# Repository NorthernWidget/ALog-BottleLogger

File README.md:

ALog-BottleLogger
=================

## Deprecation / update notice

The lovely ALog has a dear place in our hearts, but time flows by.

For our modern supported data loggers, see:
* [Project Margay](https://github.com/NorthernWidget-Skunkworks/Project-Margay): Small form factor ALog-like data logger, optimized for digital communications
* [Project Resnik](https://github.com/NorthernWidget-Skunkworks/Project-Resnik): Data logger for large installations, solar power, and telemetry

## ALog BottleLogger Basic Information

The ALog BottleLogger is an Arduino-based low-power field environmental data logging platform.

This repository contains hardware design files, centered around:
* Electronic schematics
* Circuit board layouts

In addition, the following are supplied, but are not always kept up-to-date in the main branch:
* Bill of materials (electronic components)
* Gerber files for circuit board production
* Pick-and-place files

## Layout Overview for End-Users

<!--

## Significant components

-->

## Citation

If you use this data logger in a publication, please cite:

**Wickert, A. D. (2014), [The ALog: Inexpensive, Open-Source, Automated Data Collection in the Field](https://doi.org/10.1890/0012-9623-95.2.68), *Bull. Ecol. Soc. Am.*, *95*(2), 68–78, doi:10.1890/0012-9623-95.2.68.**

**Wickert, A. D., C. T. Sandell, B. Schulz, and G.-H. C. Ng (2019), [Open-source Arduino-compatible data loggers designed for field research](https://doi.org/10.5194/hess-23-2065-2019), *Hydrol. Earth Syst. Sci.*, *23*, 2065–2076, doi:10.5194/hess-23-2065-2019.**

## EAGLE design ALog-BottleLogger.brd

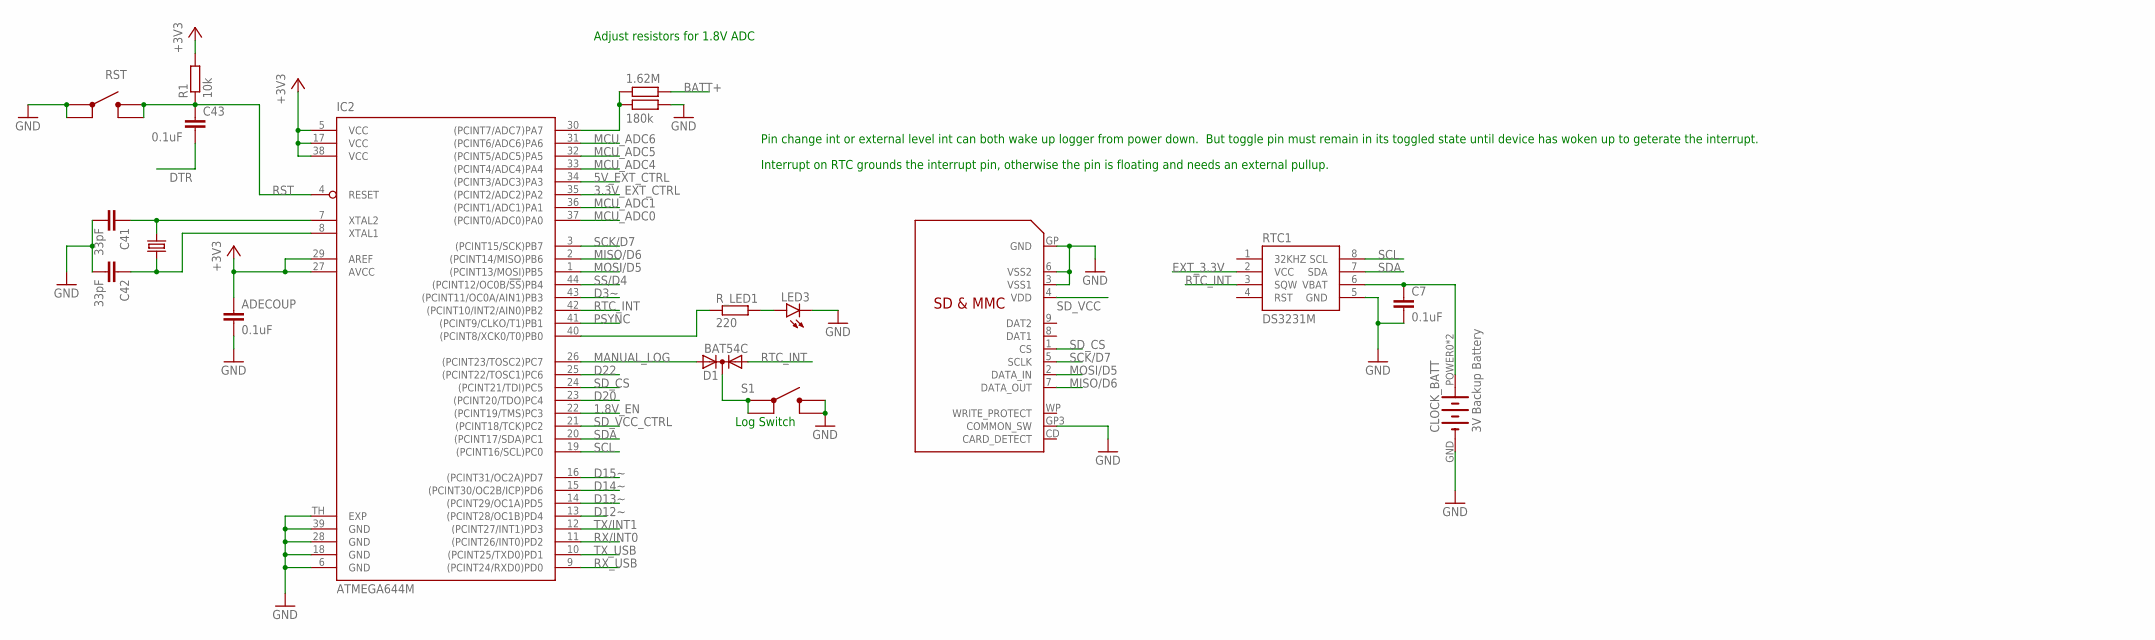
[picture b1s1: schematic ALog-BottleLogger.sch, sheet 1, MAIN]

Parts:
ADECOUP: 0.1uF; C0603
C7, C43: 0.1uF; C0603
C41, C42: 33pF; C0603
CLOCK_BATT: 3V Backup Battery; LINX_BAT-HLD-012-SMT
D1: BAT54C; SOT23C
IC2: ATMEGA644M; MLF44-TH
LED3: LED1206; LED-1206
Q3: CRYSTALHC49UP; HC49UP
R1: 10k; R0603
R18: 1.62M; R0603
R19: 180k; R0603
RTC1: DS3231M; SO08
R_LED1: 220; R0603
S1: SWITCHC&K_400GF; SWITCH_4.2X3.2
SD: SDMMC06132; 06132
U$4: SWITCHC&K_400GF; SWITCH_4.2X3.2

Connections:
1.8V_EN: IC2.22 ((PCINT19/TMS)PC3); also elsewhere on the board
3.3V_EXT_CTRL: IC2.35 ((PCINT2/ADC2)PA2); also elsewhere on the board
5V_EXT_CTRL: IC2.34 ((PCINT3/ADC3)PA3); also elsewhere on the board
+3V3: ADECOUP.1, IC2.5 (VCC), IC2.17 (VCC), IC2.27 (AVCC), IC2.29 (AREF), IC2.38 (VCC), R1.2; also elsewhere on the board
ADC16: IC2.30 ((PCINT7/ADC7)PA7), R18.1, R19.1
BATT+: R18.2; also elsewhere on the board
D3~: IC2.43 ((PCINT11/OC0A/AIN1)PB3); also elsewhere on the board
D12~: IC2.13 ((PCINT28/OC1B)PD4); also elsewhere on the board
D13~: IC2.14 ((PCINT29/OC1A)PD5); also elsewhere on the board
D14~: IC2.15 ((PCINT30/OC2B/ICP)PD6); also elsewhere on the board
D15~: IC2.16 ((PCINT31/OC2A)PD7); also elsewhere on the board
D20: IC2.23 ((PCINT20/TDO)PC4)
D22: IC2.25 ((PCINT22/TOSC1)PC6)
DTR: C43.2; also elsewhere on the board
EXT_3.3V: RTC1.2 (VCC); also elsewhere on the board
GND: ADECOUP.2, C7.2, C41.2, C42.2, CLOCK_BATT.GND (-), IC2.6 (GND), IC2.18 (GND), IC2.28 (GND), IC2.39 (GND), IC2.TH (EXP), LED3.C, R19.2, RTC1.5 (GND), S1.P$3 (3), S1.P$4 (4), SD.3 (VSS1), SD.6 (VSS2), SD.GP (GND), SD.GP3 (COMMON_SW), U$4.P$1 (1), U$4.P$2 (2); also elsewhere on the board
LED+1: LED3.A, R_LED1.2
MANUAL_LOG: D1.2 (A2), IC2.26 ((PCINT23/TOSC2)PC7)
MCU_ADC0: IC2.37 ((PCINT0/ADC0)PA0); also elsewhere on the board
MCU_ADC1: IC2.36 ((PCINT1/ADC1)PA1)
MCU_ADC4: IC2.33 ((PCINT4/ADC4)PA4)
MCU_ADC5: IC2.32 ((PCINT5/ADC5)PA5)
MCU_ADC6: IC2.31 ((PCINT6/ADC6)PA6)
MISO/D6: IC2.2 ((PCINT14/MISO)PB6), SD.7 (DATA_OUT); also elsewhere on the board
MOSI/D5: IC2.1 ((PCINT13/MOSI)PB5), SD.2 (DATA_IN); also elsewhere on the board
unnamed: IC2.40 ((PCINT8/XCK0/T0)PB0), R_LED1.1
unnamed: C7.1, CLOCK_BATT.POWER0 (+), CLOCK_BATT.POWER1 (+), RTC1.6 (VBAT)
unnamed: D1.3 (K), S1.P$1 (1), S1.P$2 (2)
PSYNC: IC2.41 ((PCINT9/CLKO/T1)PB1); also elsewhere on the board
RST: C43.1, IC2.4 (RESET), R1.1, U$4.P$3 (3), U$4.P$4 (4); also elsewhere on the board
RTC_INT: D1.1 (A1), IC2.42 ((PCINT10/INT2/AIN0)PB2), RTC1.3 (SQW)
RX/INT0: IC2.11 ((PCINT26/INT0)PD2); also elsewhere on the board
RX_USB: IC2.9 ((PCINT24/RXD0)PD0); also elsewhere on the board
SCK/D7: IC2.3 ((PCINT15/SCK)PB7), SD.5 (SCLK); also elsewhere on the board
SCL: IC2.19 ((PCINT16/SCL)PC0), RTC1.8 (SCL); also elsewhere on the board
SDA: IC2.20 ((PCINT17/SDA)PC1), RTC1.7 (SDA); also elsewhere on the board
SD_CS: IC2.24 ((PCINT21/TDI)PC5), SD.1 (CS)
SD_VCC: SD.4 (VDD); also elsewhere on the board
SD_VCC_CTRL: IC2.21 ((PCINT18/TCK)PC2); also elsewhere on the board
SS/D4: IC2.44 ((PCINT12/OC0B/!SS!)PB4); also elsewhere on the board
TX/INT1: IC2.12 ((PCINT27/INT1)PD3); also elsewhere on the board
TX_USB: IC2.10 ((PCINT25/TXD0)PD1); also elsewhere on the board
XTAL1: C42.1, IC2.8 (XTAL1), Q3.1
XTAL2: C41.1, IC2.7 (XTAL2), Q3.2

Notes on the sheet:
Log Switch
Adjust resistors for 1.8V ADC
Pin change int or external level int can both wake up logger from power down. But toggle pin must remain in its toggled state until device has woken up to geterate the interrupt.
Interrupt on RTC grounds the interrupt pin, otherwise the pin is floating and needs an external pullup.

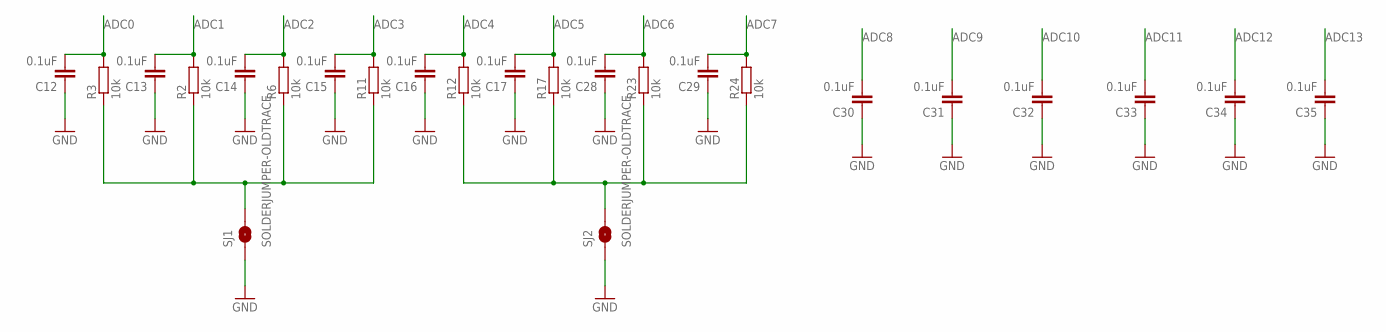
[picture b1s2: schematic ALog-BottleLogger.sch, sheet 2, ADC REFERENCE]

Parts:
C12, C13, C14, C15, C16, C17, C28, C29, C30, C31, C32, C33, C34, C35: 0.1uF; C0603
R2, R3, R6, R11, R12, R17, R23, R24: 10k; R0603
SJ1, SJ2: SOLDERJUMPER-OLDTRACE; SJ_2S-TRACE

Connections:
ADC0: C12.2, R3.2; also elsewhere on the board
ADC1: C13.2, R2.2; also elsewhere on the board
ADC2: C14.2, R6.2; also elsewhere on the board
ADC3: C15.2, R11.2; also elsewhere on the board
ADC4: C16.2, R12.2; also elsewhere on the board
ADC5: C17.2, R17.2; also elsewhere on the board
ADC6: C28.2, R23.2; also elsewhere on the board
ADC7: C29.2, R24.2; also elsewhere on the board
ADC8: C30.2; also elsewhere on the board
ADC9: C31.2; also elsewhere on the board
ADC10: C32.2; also elsewhere on the board
ADC11: C33.2; also elsewhere on the board
ADC12: C34.2; also elsewhere on the board
ADC13: C35.2; also elsewhere on the board
GND: C12.1, C13.1, C14.1, C15.1, C16.1, C17.1, C28.1, C29.1, C30.1, C31.1, C32.1, C33.1, C34.1, C35.1, SJ1.1, SJ2.1; also elsewhere on the board
unnamed: R12.1, R17.1, R23.1, R24.1, SJ2.2
unnamed: R2.1, R3.1, R6.1, R11.1, SJ1.2

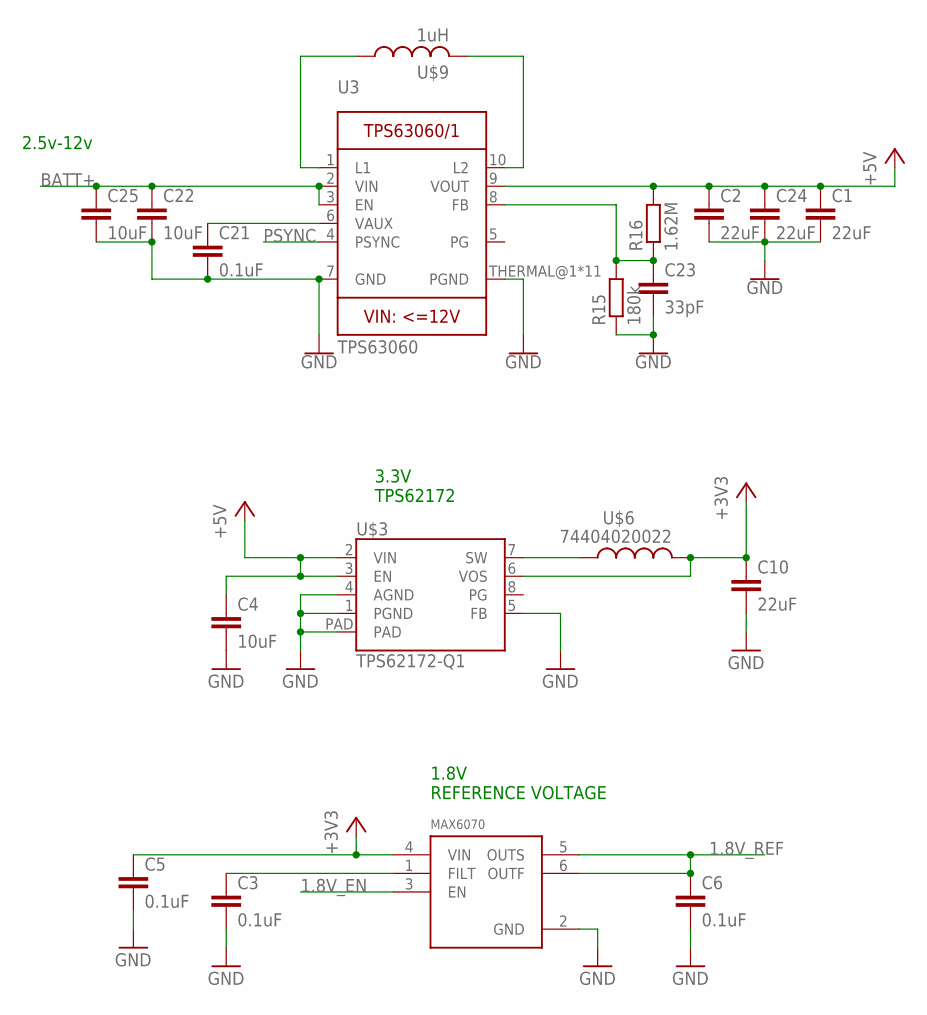
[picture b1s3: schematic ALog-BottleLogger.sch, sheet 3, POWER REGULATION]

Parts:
C1, C2, C10, C24: 22uF; C0805
C3, C5, C6, C21: 0.1uF; C0603
C4, C22, C25: 10uF; C0805
C23: 33pF; C0603
R15: 180k; R0603
R16: 1.62M; R0603
U3: TPS63060; PWSON-N10
U$2: MAX6070AAUT18; SOT23-6L
U$3: TPS62172-Q1; WSON-8-PAD
U$6: 74404020022; WURTH2.2UF
U$9: 1uH; WE-MAIA(4.1X4.1)

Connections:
1.8V_EN: U$2.3 (EN); also elsewhere on the board
1.8V_REF: C6.1, U$2.5 (OUTS), U$2.6 (OUTF); also elsewhere on the board
+3V3: C5.1, C10.1, U$2.4 (VIN), U$3.6 (VOS), U$6.2; also elsewhere on the board
+5V: C1.1, C2.1, C4.1, C24.1, R16.2, U3.9 (VOUT), U$3.2 (VIN), U$3.3 (EN); also elsewhere on the board
BATT+: C22.1, C25.1, U3.2 (VIN), U3.3 (EN); also elsewhere on the board
GND: C1.2, C2.2, C3.2, C4.2, C5.2, C6.2, C10.2, C21.2, C22.2, C23.2, C24.2, C25.2, R15.1, U3.7 (GND), U3.THERMAL@1 (PGND), U3.THERMAL@5 (PGND), U3.THERMAL@6 (PGND), U3.THERMAL@7 (PGND), U3.THERMAL@8 (PGND), U3.THERMAL@9 (PGND), U3.THERMAL@10 (PGND), U3.THERMAL@11 (PGND), U3.THERMAL@12 (PGND), U3.THERMAL@13 (PGND), U3.THERMAL@14 (PGND), U$2.2 (GND), U$3.1 (PGND), U$3.4 (AGND), U$3.5 (FB), U$3.PAD; also elsewhere on the board
unnamed 42: U$3.7 (SW), U$6.1; also elsewhere on the board
unnamed: C21.1, U3.6 (VAUX)
unnamed: C23.1, R15.2, R16.1, U3.8 (FB)
unnamed 67: U3.1 (L1), U$9.P$1 (1); also elsewhere on the board
unnamed 71: U3.10 (L2), U$9.P$2 (2); also elsewhere on the board
unnamed: C3.1, U$2.1 (FILT)
PSYNC: U3.4 (PSYNC); also elsewhere on the board

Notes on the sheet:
2.5v-12v
3.3V TPS62172
1.8V REFERENCE VOLTAGE

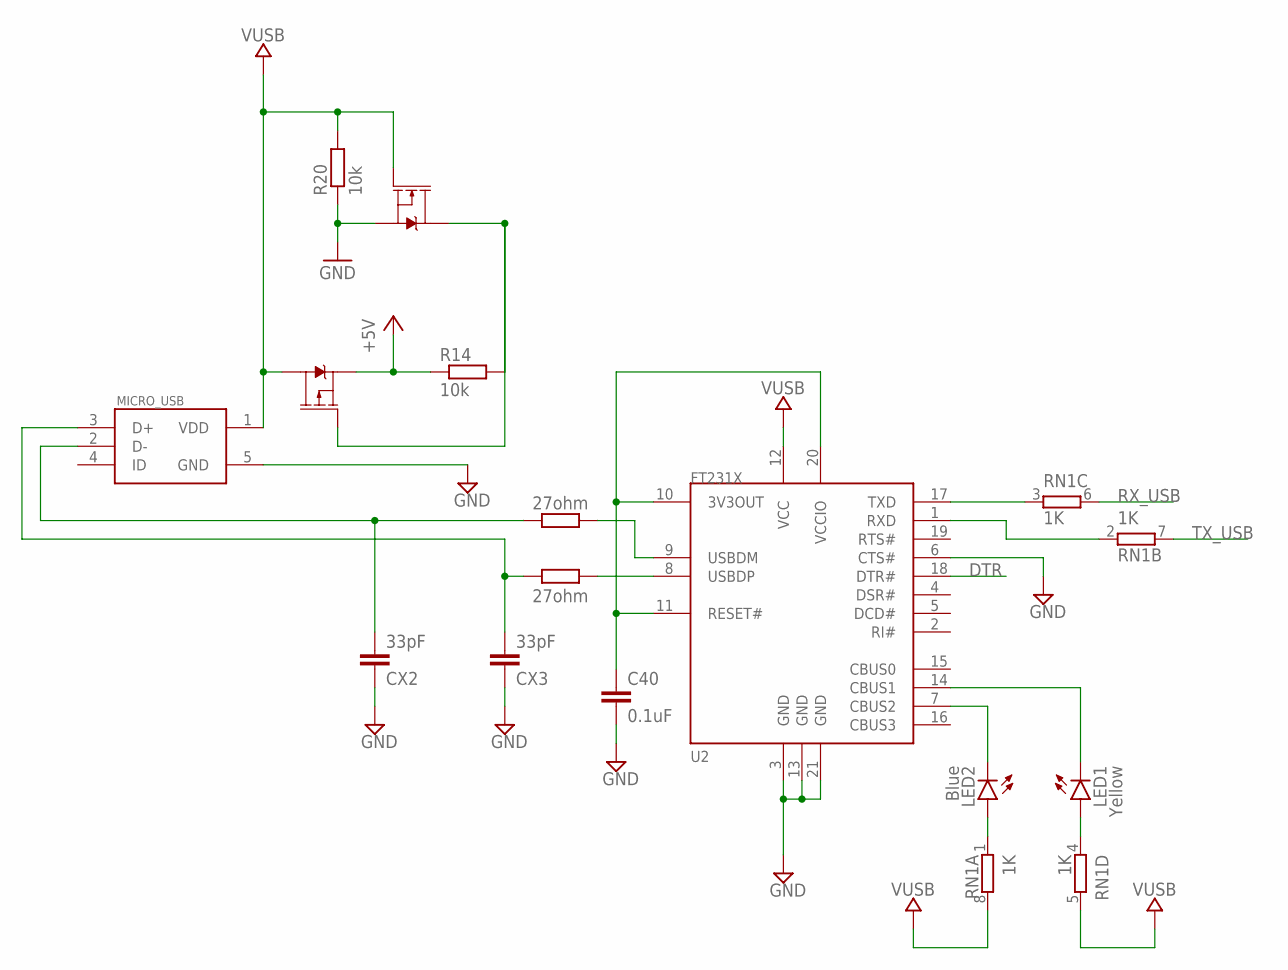
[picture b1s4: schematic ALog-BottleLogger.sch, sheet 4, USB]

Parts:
C40: 0.1uF; C0603
CX2, CX3: 33pF; C0603
D+: 27ohm; R0603
D-: 27ohm; R0603
LED1: Yellow; LED-0603
LED2: Blue; LED-0603
MICRO_USB: MICRO_USB_LONGPADS; 10118194-0001LF_10118194-0001LF_LONGER_PADS
Q11: MOSFET-NCH-BSS138; SOT23-3
Q12: MOSFET_PCH-IRLML2244; SOT23-3
R14, R20: 10k; R0603
RN1: 1K; 0603-ARC
U2: FT231X-Q; QFN20

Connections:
+5V: Q12.2 (S), R14.1; also elsewhere on the board
DTR: U2.18 (DTR#); also elsewhere on the board
GND: C40.2, CX2.1, CX3.1, MICRO_USB.5 (GND), Q11.2 (S), R20.1, U2.3 (GND), U2.6 (CTS#), U2.13 (GND), U2.21 (GND); also elsewhere on the board
unnamed: LED2.A, RN1.1
unnamed: LED1.A, RN1.4 (1)
unnamed: RN1.3 (1), U2.17 (TXD)
unnamed: Q11.3 (D), Q12.1 (G), R14.2
unnamed: CX3.2, D+.2, MICRO_USB.3 (D+)
unnamed: CX2.2, D-.2, MICRO_USB.2 (D-)
unnamed: D+.1, U2.8 (USBDP)
unnamed: RN1.2 (1), U2.1 (RXD)
unnamed: C40.1, U2.10 (3V3OUT), U2.11 (RESET#), U2.20 (VCCIO)
unnamed: LED2.C, U2.7 (CBUS2)
unnamed: LED1.C, U2.14 (CBUS1)
unnamed: D-.1, U2.9 (USBDM)
RX_USB: RN1.6 (2); also elsewhere on the board
TX_USB: RN1.7 (2); also elsewhere on the board
VUSB: MICRO_USB.1 (VDD), Q11.1 (G), Q12.3 (D), R20.2, RN1.5 (2), RN1.8 (2), U2.12 (VCC)

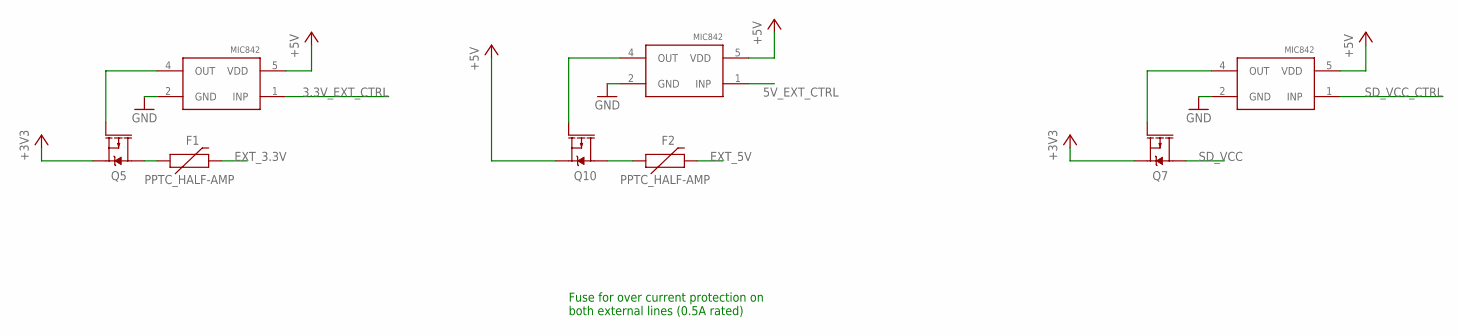
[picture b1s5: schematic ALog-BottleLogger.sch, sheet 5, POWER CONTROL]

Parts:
F1, F2: PPTC_HALF-AMP; 1206
Q5, Q7, Q10: MOSFET_PCH-IRLML2244; SOT23-3
U$1, U$12, U$16: MIC842; DCK_R-PDSO-G5

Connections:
3.3V_EXT_CTRL: U$12.1 (INP); also elsewhere on the board
5V_EXT_CTRL: U$1.1 (INP); also elsewhere on the board
+3V3: Q5.2 (S), Q7.2 (S); also elsewhere on the board
+5V: Q10.2 (S), U$1.5 (VDD), U$12.5 (VDD), U$16.5 (VDD); also elsewhere on the board
EXT_3.3V: F1.2; also elsewhere on the board
EXT_5V: F2.2; also elsewhere on the board
GND: U$1.2 (GND), U$12.2 (GND), U$16.2 (GND); also elsewhere on the board
unnamed: Q5.1 (G), U$12.4 (OUT)
unnamed: Q10.1 (G), U$1.4 (OUT)
unnamed: F1.1, Q5.3 (D)
unnamed: Q7.1 (G), U$16.4 (OUT)
unnamed: F2.1, Q10.3 (D)
SD_VCC: Q7.3 (D); also elsewhere on the board
SD_VCC_CTRL: U$16.1 (INP); also elsewhere on the board

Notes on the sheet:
Fuse for over current protection on both external lines (0.5A rated)

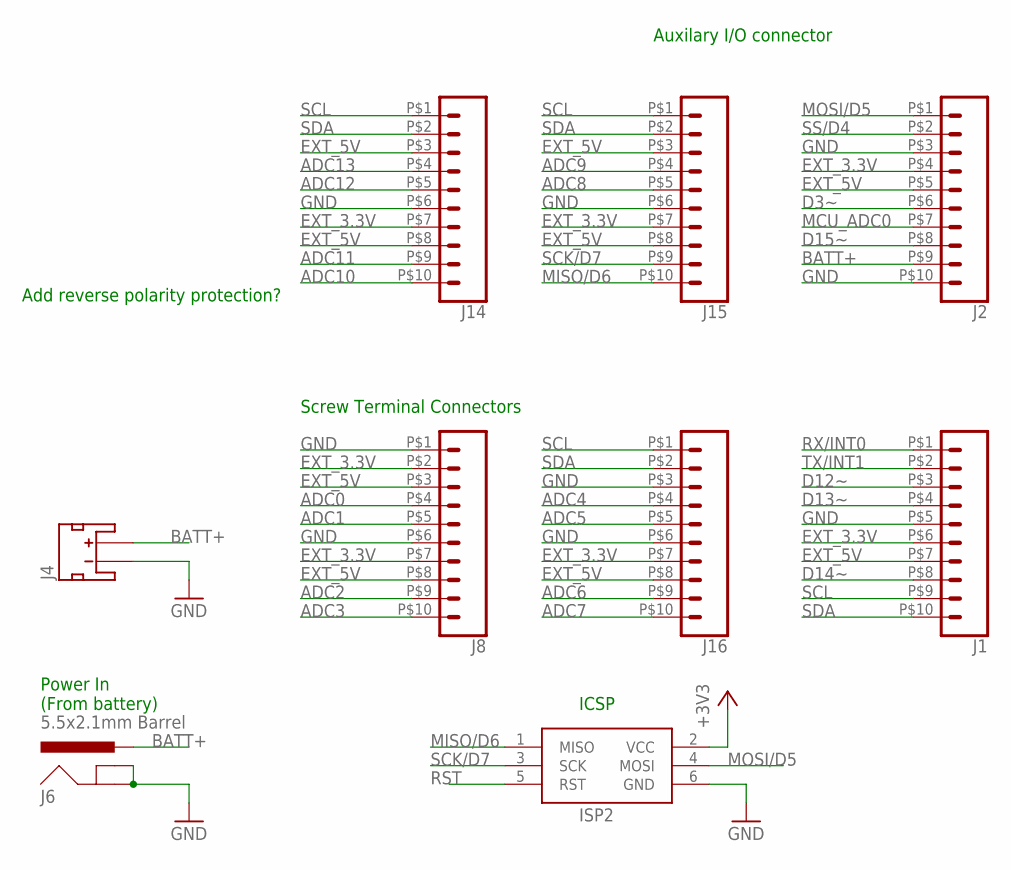
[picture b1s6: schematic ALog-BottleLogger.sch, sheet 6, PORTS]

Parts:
ISP2: AVRISP-6; AVRISP
J1, J2, J8, J14, J15, J16: CONN_103.5MM; 1X10_3.5MM_SCREW
J4: JST_2MM_MALE; JST-2-SMD
J6: 5.5x2.1mm Barrel; POWER_JACK_SMD

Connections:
+3V3: ISP2.2 (VCC); also elsewhere on the board
ADC0: J8.P$4 (4); also elsewhere on the board
ADC1: J8.P$5 (5); also elsewhere on the board
ADC2: J8.P$9 (9); also elsewhere on the board
ADC3: J8.P$10 (10); also elsewhere on the board
ADC4: J16.P$4 (4); also elsewhere on the board
ADC5: J16.P$5 (5); also elsewhere on the board
ADC6: J16.P$9 (9); also elsewhere on the board
ADC7: J16.P$10 (10); also elsewhere on the board
ADC8: J15.P$5 (5); also elsewhere on the board
ADC9: J15.P$4 (4); also elsewhere on the board
ADC10: J14.P$10 (10); also elsewhere on the board
ADC11: J14.P$9 (9); also elsewhere on the board
ADC12: J14.P$5 (5); also elsewhere on the board
ADC13: J14.P$4 (4); also elsewhere on the board
BATT+: J2.P$9 (9), J4.2 (+), J6.VIN0 (PWR); also elsewhere on the board
D3~: J2.P$6 (6); also elsewhere on the board
D12~: J1.P$3 (3); also elsewhere on the board
D13~: J1.P$4 (4); also elsewhere on the board
D14~: J1.P$8 (8); also elsewhere on the board
D15~: J2.P$8 (8); also elsewhere on the board
EXT_3.3V: J1.P$6 (6), J2.P$4 (4), J8.P$2 (2), J8.P$7 (7), J14.P$7 (7), J15.P$7 (7), J16.P$7 (7); also elsewhere on the board
EXT_5V: J1.P$7 (7), J2.P$5 (5), J8.P$3 (3), J8.P$8 (8), J14.P$3 (3), J14.P$8 (8), J15.P$3 (3), J15.P$8 (8), J16.P$8 (8); also elsewhere on the board
GND: ISP2.6 (GND), J1.P$5 (5), J2.P$3 (3), J2.P$10 (10), J4.1 (-), J6.GND (GNDBREAK), J6.P$4 (GND), J8.P$1 (1), J8.P$6 (6), J14.P$6 (6), J15.P$6 (6), J16.P$3 (3), J16.P$6 (6); also elsewhere on the board
MCU_ADC0: J2.P$7 (7); also elsewhere on the board
MISO/D6: ISP2.1 (MISO), J15.P$10 (10); also elsewhere on the board
MOSI/D5: ISP2.4 (MOSI), J2.P$1 (1); also elsewhere on the board
RST: ISP2.5 (RST); also elsewhere on the board
RX/INT0: J1.P$1 (1); also elsewhere on the board
SCK/D7: ISP2.3 (SCK), J15.P$9 (9); also elsewhere on the board
SCL: J1.P$9 (9), J14.P$1 (1), J15.P$1 (1), J16.P$1 (1); also elsewhere on the board
SDA: J1.P$10 (10), J14.P$2 (2), J15.P$2 (2), J16.P$2 (2); also elsewhere on the board
SS/D4: J2.P$2 (2); also elsewhere on the board
TX/INT1: J1.P$2 (2); also elsewhere on the board

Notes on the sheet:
Add reverse polarity protection?
Screw Terminal Connectors
ICSP
Auxilary I/O connector
Power In (From battery)

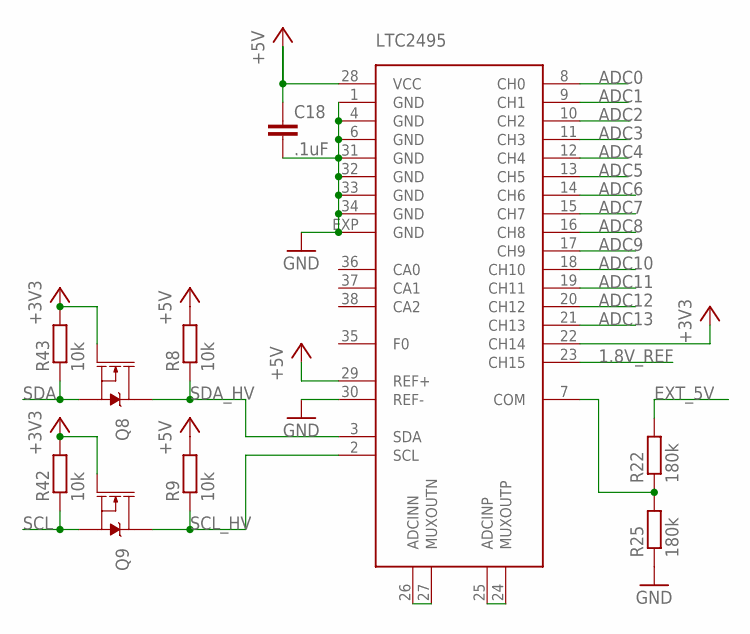
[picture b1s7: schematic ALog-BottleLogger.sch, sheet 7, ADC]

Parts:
C18: .1uF; C0603
Q8, Q9: MOSFET-NCH-BSS138; SOT23-3
R8, R9, R42, R43: 10k; R0603
R22: 180k; R0603
R25: 180k; R0603; MPN AC0603FR-07180KL; DIGIKEY 311-180KLDCT-ND
U$7: LTC2495; QFN38-5X7

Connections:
1.8V_REF: U$7.23 (CH15); also elsewhere on the board
+3V3: Q8.1 (G), Q9.1 (G), R42.2, R43.2, U$7.22 (CH14); also elsewhere on the board
+5V: C18.1, R8.2, R9.2, U$7.28 (VCC), U$7.29 (REF+); also elsewhere on the board
ADC0: U$7.8 (CH0); also elsewhere on the board
ADC1: U$7.9 (CH1); also elsewhere on the board
ADC2: U$7.10 (CH2); also elsewhere on the board
ADC3: U$7.11 (CH3); also elsewhere on the board
ADC4: U$7.12 (CH4); also elsewhere on the board
ADC5: U$7.13 (CH5); also elsewhere on the board
ADC6: U$7.14 (CH6); also elsewhere on the board
ADC7: U$7.15 (CH7); also elsewhere on the board
ADC8: U$7.16 (CH8); also elsewhere on the board
ADC9: U$7.17 (CH9); also elsewhere on the board
ADC10: U$7.18 (CH10); also elsewhere on the board
ADC11: U$7.19 (CH11); also elsewhere on the board
ADC12: U$7.20 (CH12); also elsewhere on the board
ADC13: U$7.21 (CH13); also elsewhere on the board
EXT_5V: R22.2; also elsewhere on the board
GND: C18.2, R25.1, U$7.1 (GND), U$7.4 (GND), U$7.6 (GND), U$7.30 (REF-), U$7.31 (GND), U$7.32 (GND), U$7.33 (GND), U$7.34 (GND), U$7.EXP (GND); also elsewhere on the board
unnamed: R22.1, R25.2, U$7.7 (COM)
unnamed: U$7.24 (MUXOUTP), U$7.25 (ADCINP)
unnamed: U$7.26 (ADCINN), U$7.27 (MUXOUTN)
SCL: Q9.2 (S), R42.1; also elsewhere on the board
SCL_HV: Q9.3 (D), R9.1, U$7.2 (SCL)
SDA: Q8.2 (S), R43.1; also elsewhere on the board
SDA_HV: Q8.3 (D), R8.1, U$7.3 (SDA)

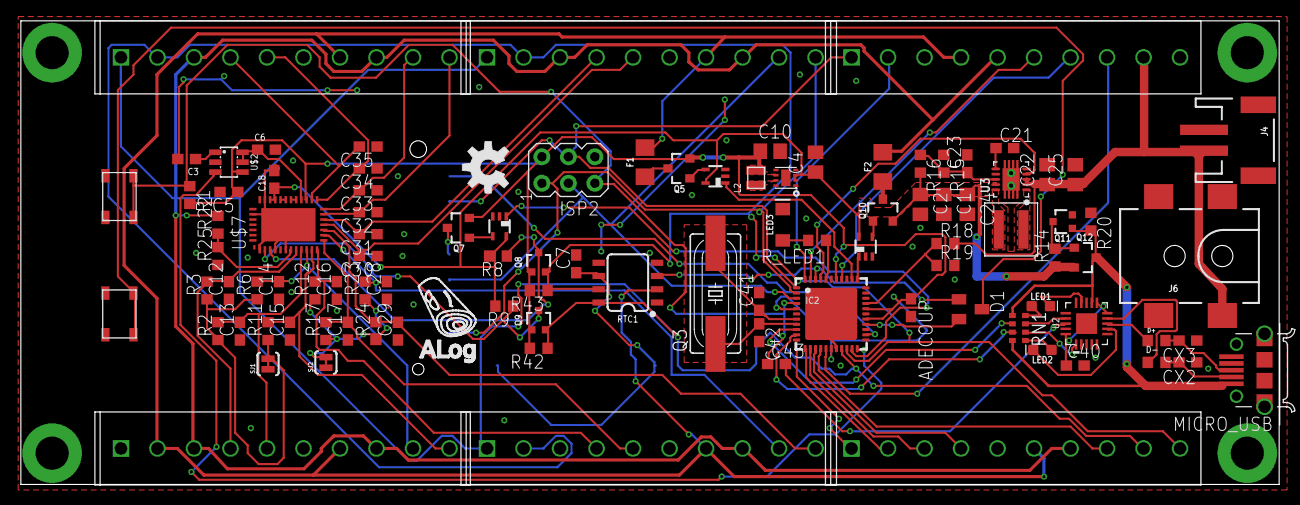
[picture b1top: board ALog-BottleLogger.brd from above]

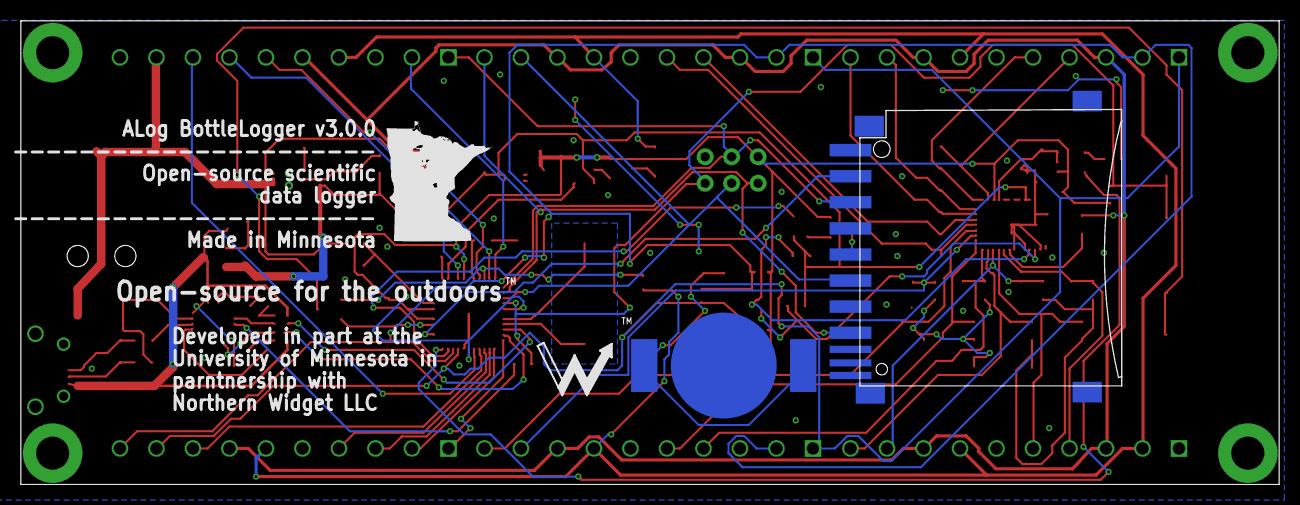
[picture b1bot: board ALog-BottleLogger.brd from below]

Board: 2 copper layers, 120.7 x 44.5 mm, 106 parts (3 on the bottom side), 86 nets.

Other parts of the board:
L1: 1uH; WE-MAIA(4.1X4.1)
L2: 2.2uH; 0806
LOGO2: OSHW-LOGOM; OSHW-LOGO-M
U$13: MN_SILK
U$14: ALOG_LOGO_V1_5.5MM; ALOG_LOGO_V1_SMALL
U$15: NWLOGO_MED

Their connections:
+3V3: L2.P$2; also elsewhere on the board
unnamed 42: L2.P$1; also elsewhere on the board
unnamed 67: L1.P$1; also elsewhere on the board
unnamed 71: L1.P$2; also elsewhere on the board

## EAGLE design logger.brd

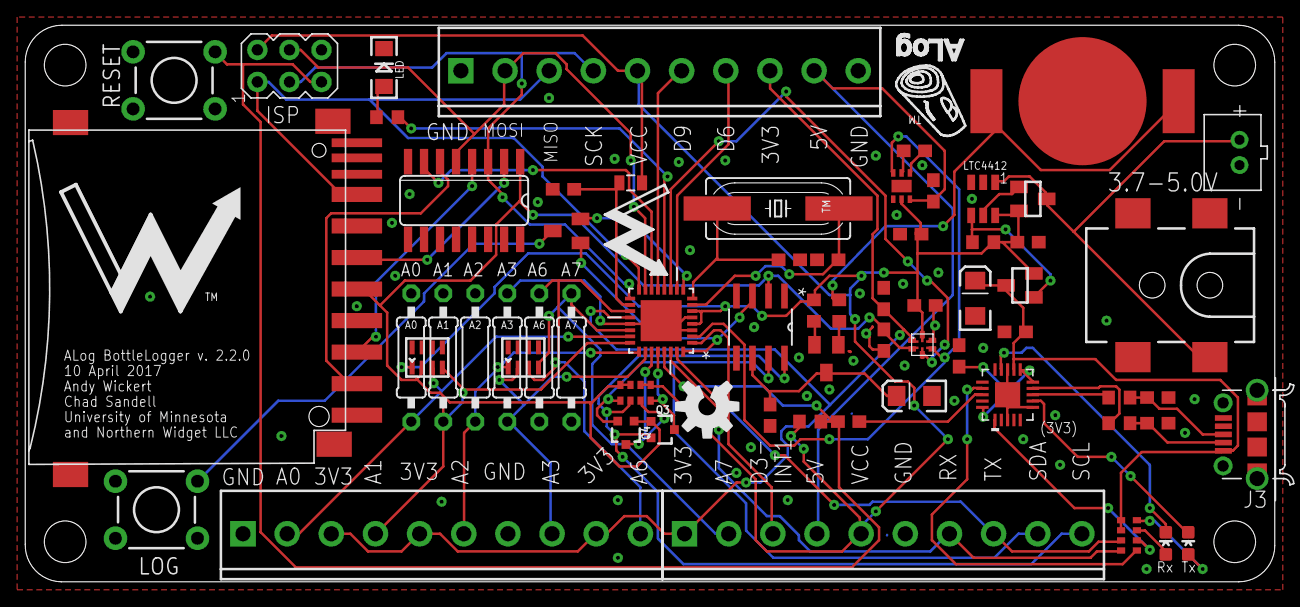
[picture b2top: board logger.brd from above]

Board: 2 copper layers, 99.0 x 44.1 mm, 74 parts (0 on the bottom side), 60 nets.

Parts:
3V3: MIC5380_LARGE_PADS; 6-TMLF_SMD_PADS
5V_CHARGE_PUMP: 5V; SON65P200X200X80-7N
A0, A1, A2, A3, A6, A7: 0207/10
ADECOUP: 0.1uF; C0603
C1, C17: 0.1uF; C0603
C14, C15: 10nF; CECJ-CTS-031817
C21: 10uF; EIA3216
CLOCK_BATT: 3V Backup Battery; LINX_BAT-HLD-012-SMT
CLOCK_BATT_DECOUP: 0.1uF; C0603
CLOCK_BATT_DECOUPLE: 10uF; EIA3216
CLOCK_CIN1, CLOCK_CIN2, CLOCK_CIN3: 1uF; C0603
CN1: JST-PH-2-THM
COUT: 1uF; C0603
COUT1: 0.1uF; C0603
CX0, CX1, CX2, CX3: 33pF; C0603
C_BOOST_1: 4.7uF; C0603
C_BOOST_2, C_BOOST_3: 2.2uF; C0603
D1: BAT54C; SOT23C
D2: BAT54; SOT23C
D+: 27ohm; R0603
D-: 27ohm; R0603
H0, H1, H3: SCREWTERMINAL-3.5MM-8
ISP: AVRISP-6; AVRISP
J1: 5.5x2.1mm Barrel; POWER_JACK_SMD
J3: 10118194-0001LF; FRAMATOME_10118194-0001LF
JP1, JP2, JP3, JP4: STAND-OFF
LED: LED-1206
LED1: Yellow; LED-0603
LED2: Blue; LED-0603
LOG: LOG; TACTILE-PTH
LOGO1: OSHW-LOGOM; OSHW-LOGO-M
LSHIFT: 4050D; SO16
LTC4412: LTC4412ES6; TSOT23-6
L_LPF: 10uH; 0805
MCU: ATMEGA328P-MU; QFN50P500X500X100-33N
Q1, Q2: FDN360P; SUPER-SOT3
Q3, Q4: 310mA/60V/1.6Ω; SOT323
RCKL1: 220; R0603
RCLK2: 220; R0603
RESET: Reset; TACTILE-PTH
RN1: 1K; 0603-ARC
RN2: 3.3K; 0603-ARC
RSTAT: 470k; R0603
R_LED: 220; R0603
R_RESET: 10k; R0603
SD: SDMMC06132; 06132
U1: DS3231MZ/V+T; 21-0041B_8
U2: FT231X-Q; QFN20
U$1: NWLOGO
U$2: ALOG_LOGO_V1_5.5MM; ALOG_LOGO_V1_SMALL
U$3: NWLOGO_MED
U$8: ALOG_BACK_SILK; ALOG_BACK_SILK_GENERIC
U$9: 2.2.0
XTAL: 8MHz; HC49UP

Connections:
5V: 5V_CHARGE_PUMP.3, C_BOOST_3.2, H1.4, H3.9
+3V3: 3V3.1, 3V3.7, CLOCK_CIN2.1, H0.3, H0.5, H0.9, H1.1, H3.8, MCU.20
A0: A0.2, C14.C1, H0.2, MCU.23
A1: A1.2, C14.D1, H0.4, MCU.24
A2: A2.2, C15.A1, H0.6, MCU.25
A3: A3.2, C15.B1, H0.8, MCU.26
A6: A6.1, C15.C1, H0.10, MCU.19
A7: A7.1, C15.D1, H1.2, MCU.22
AVCC: ADECOUP.1, L_LPF.2, MCU.18
BAT: CLOCK_BATT_DECOUP.1, CLOCK_BATT_DECOUPLE.A, D1.3, U1.6
CLK: H3.4, ISP.3, LSHIFT.3, MCU.17
CS-SD: LSHIFT.7, MCU.14
D3-INT1: H1.3, MCU.1
D4-SENSE_LDO_SWITCH: 3V3.4, 3V3.10, 5V_CHARGE_PUMP.6, MCU.2
D5_MANUAL_LOG: D2.2, MCU.9
D6-EXT: H3.7, MCU.10
D7-CLOCK_SD_SWITCH: 3V3.3, 3V3.9, MCU.11
D8_LED: MCU.12, R_LED.1
D9-CS-EXT: H3.6, MCU.13
DI: H3.2, ISP.4, LSHIFT.5, MCU.15
DO: H3.3, ISP.1, MCU.16, SD.7
DTR: COUT1.1, U2.18
GND: 3V3.5, 3V3.11, 5V_CHARGE_PUMP.1, 5V_CHARGE_PUMP.7, A0.1, A1.1, A2.1, A3.1, A6.2, A7.2, ADECOUP.2, C1.2, C14.A2, C14.B2, C14.C2, C14.D2, C15.A2, C15.B2, C15.C2, C15.D2, C17.2, C21.C, CLOCK_BATT.GND, CLOCK_BATT_DECOUP.2, CLOCK_BATT_DECOUPLE.C, CLOCK_CIN1.2, CLOCK_CIN2.2, CLOCK_CIN3.2, CN1.2, COUT.2, CX0.1, CX1.1, CX2.1, CX3.1, C_BOOST_1.1, C_BOOST_3.1, H0.1, H0.7, H1.6, H3.1, H3.10, ISP.6, J1.GND, J1.P$4, J3.5, LED.C, LOG.1, LSHIFT.8, LSHIFT.9, LSHIFT.11, LSHIFT.14, LTC4412.2, LTC4412.3, MCU.3, MCU.5, MCU.21, MCU.33, RESET.1, SD.3, SD.6, SD.GP, SD.GP3, U1.5, U2.3, U2.6, U2.13, U2.21
INT0: D2.1, MCU.32, U1.3
LED+: LED.A, R_LED.2
unnamed: D1.1, RCLK2.1
unnamed: D-.1, U2.9
unnamed: CX3.2, D+.2, J3.3
unnamed: CX2.2, D-.2, J3.2
unnamed: LED2.A, RN1.4
unnamed: LED2.C, U2.7
unnamed: LTC4412.4, Q2.1, RSTAT.1
unnamed: LTC4412.5, Q1.1
unnamed: LED1.A, RN1.3
unnamed: LED1.C, U2.14
unnamed: D2.3, LOG.3
unnamed: 5V_CHARGE_PUMP.4, C_BOOST_2.2
unnamed: 5V_CHARGE_PUMP.5, C_BOOST_2.1
unnamed: D+.1, U2.8
unnamed: C1.1, U2.10, U2.11, U2.20
unnamed: RN1.1, U2.17
unnamed: RN1.2, U2.1
unnamed: D1.2, RCKL1.1
RESET: COUT1.2, ISP.5, MCU.29, RESET.3, R_RESET.1
RTC_BATT: CLOCK_BATT.POWER0, CLOCK_BATT.POWER1, RCLK2.2
RX-I: H1.7, MCU.30, RN1.8
SCL: H1.10, Q3.2, RN2.6, U1.8
SCL_MCU: MCU.28, Q3.3, RN2.8
SDA: H1.9, Q4.2, RN2.5, U1.7
SDA_MCU: MCU.27, Q4.3, RN2.7
SD_CLK: LSHIFT.2, SD.5
SD_CS: LSHIFT.6, SD.1
SD_DI: LSHIFT.4, SD.2
TX-O: H1.8, MCU.31, RN1.7
VBAT: CN1.1, J1.VIN0, LTC4412.1, Q1.3
VCC: 3V3.6, 3V3.12, 5V_CHARGE_PUMP.2, C14.A1, CLOCK_CIN1.1, COUT.1, C_BOOST_1.2, H1.5, H3.5, ISP.2, LTC4412.6, L_LPF.1, MCU.4, MCU.6, Q1.2, Q2.2, RCKL1.2, RN2.1, RN2.2, RSTAT.2, R_RESET.2
VDD: 3V3.2, 3V3.8, C14.B1, CLOCK_CIN3.1, LSHIFT.1, Q3.1, Q4.1, RN2.3, RN2.4, SD.4, U1.2
VUSB: C17.1, C21.A, J3.1, Q2.3, RN1.5, RN1.6, U2.12
X0: CX0.2, MCU.7, XTAL.2
X1: CX1.2, MCU.8, XTAL.1

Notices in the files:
parts and their libraries:
SparkFun-LED: Licensing: Creative Commons ShareAlike 4.0 International - https://creativecommons.org/licenses/by-sa/4.0
SparkFun-Aesthetics: Licensing: CC v3.0 Share-Alike You are welcome to use this library for commercial purposes.
rc-master-smd: Copyright (C) 2007, Bob Starr
